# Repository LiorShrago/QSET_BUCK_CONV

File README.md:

# QSET_BUCK_CONV
Buck Converter which can have an input votlage of 12V-9V and then step-down the voltage to 5V. There is also an E-Fuse on the output of the Buck converter for extra safety.

Inside the folder there are 3 more folder.
1 - One folder that all the EAGLE library files needed to see the schematic

2 - One folder holds the EAGLE schematic and PCB files

3 - One folder has the TinaTi, spice files used to test the buck converter before manufcaturing the PCB. TinaTi is a spice software that TI offers for their components,
it helped check that the Buck converter transient response and how bad its Output Voltage ripple would be under various loads.

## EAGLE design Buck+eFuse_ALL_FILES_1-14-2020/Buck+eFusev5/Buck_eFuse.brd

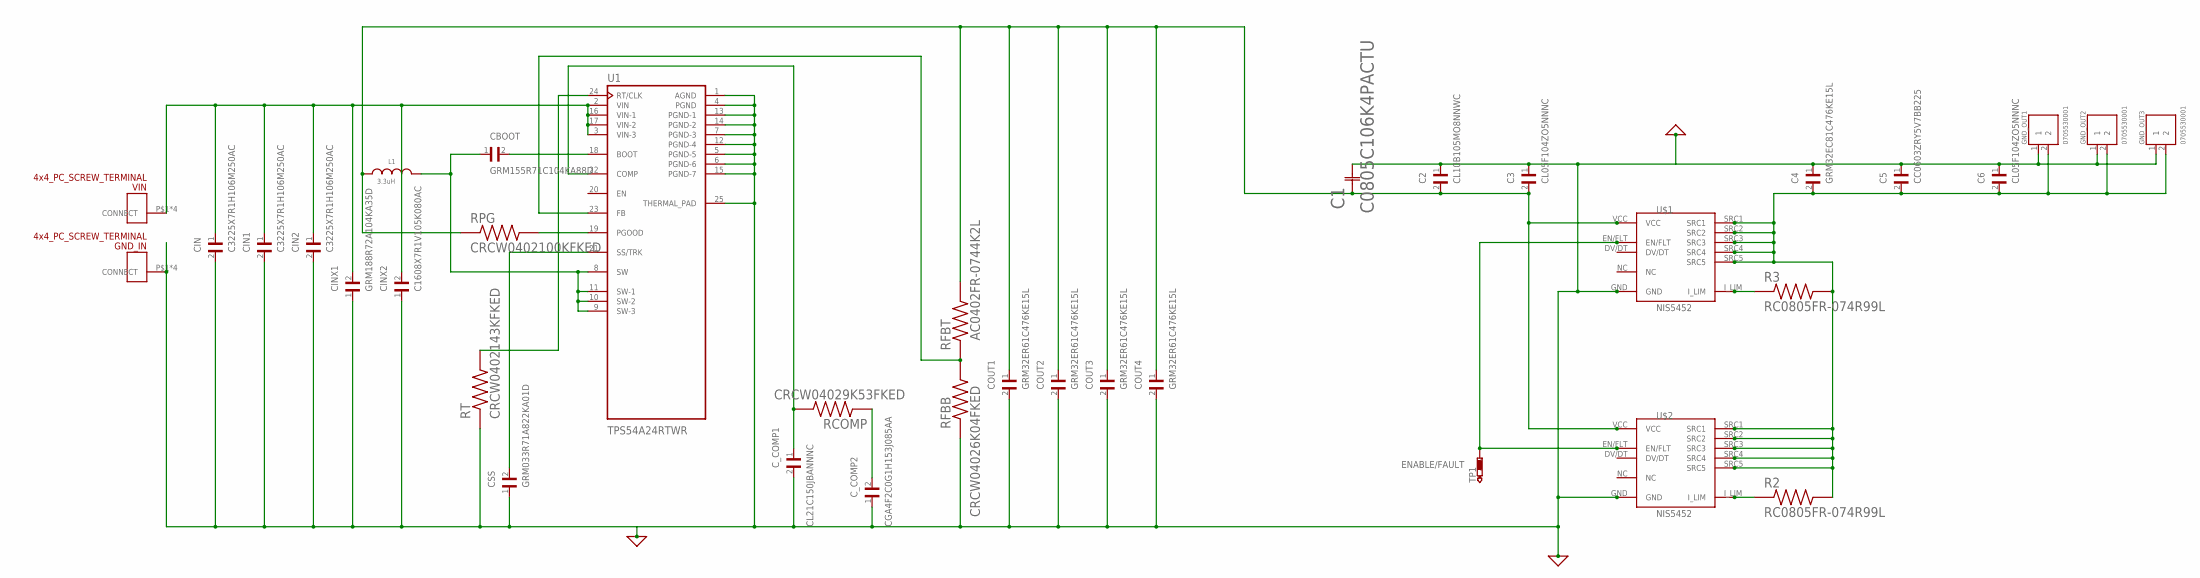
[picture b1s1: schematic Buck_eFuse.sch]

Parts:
C1: C0805C106K4PACTU; CAP_C0805
C2: CL10B105MO8NNWC; CAPC1608X90N
C3, C6: CL05F104ZO5NNNC; CAPC1005X55N
C4: GRM32EC81C476KE15L; CAPC3225X270N
C5: CC0603ZRY5V7BB225; CAPC1608X90
CBOOT: GRM155R71C104KA88D; CAPC1005X55N
CIN, CIN1, CIN2: C3225X7R1H106M250AC; CAPC3225X280N
CINX1: GRM188R72A104KA35D; CAPC1608X90N
CINX2: C1608X7R1V105K080AC; CAPC1608X90N
COUT1, COUT2, COUT3, COUT4: GRM32ER61C476KE15L; CAPC3225X270N
CSS: GRM033R71A822KA01D; CAPC0603X33N
C_COMP1: CL21C150JBANNNC; CAPC2012X140N
C_COMP2: CGA4F2C0G1H153J085AA; CAPC2012X100N
GND_IN: 2X2_PC_SCREW_TERMINAL; SCREW_TERMINAL
GND_OUT1, GND_OUT2, GND_OUT3: 0705530001; MOLEX_0705530001
L1: 3.3uH; WE-HCC_1090
R2, R3: RC0805FR-074R99L; RESC2012X60N
RCOMP: CRCW04029K53FKED; RESC1005X40N
RFBB: CRCW04026K04FKED; RESC1005X40N
RFBT: AC0402FR-0744K2L; RESC1005X37N
RPG: CRCW0402100KFKED; RESC1005X40N
RT: CRCW0402143KFKED; RESC1005X40N
TP1: PTR1B2,54; B2,54
U1: TPS54A24RTWR; VQFN50P400X400X100-24N
U$1, U$2: NIS5452; WDFN10
VIN: 2X2_PC_SCREW_TERMINAL; SCREW_TERMINAL

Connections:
0: C1.2, C2.1, C3.1, C4.1, C5.1, C6.1, CIN.2, CIN1.2, CIN2.2, CINX1.1, CINX2.1, COUT1.2, COUT2.2, COUT3.2, COUT4.2, CSS.1, C_COMP1.2, C_COMP2.1, GND_IN.P$1, GND_IN.P$2, GND_IN.P$3, GND_IN.P$4, GND_OUT1.1, GND_OUT2.1, GND_OUT3.1, RFBB.1, RT.1, U1.1 (AGND), U1.4 (PGND), U1.5 (PGND-5), U1.6 (PGND-6), U1.7 (PGND-3), U1.12 (PGND-4), U1.13 (PGND-1), U1.14 (PGND-2), U1.15 (PGND-7), U1.25 (THERMAL_PAD), U$1.GND, U$2.GND
ENABLE/FAULT: TP1.TP, U$1.EN/FLT, U$2.EN/FLT
unnamed: CBOOT.2, U1.18 (BOOT)
unnamed: CBOOT.1, L1.2, U1.8 (SW), U1.9 (SW-3), U1.10 (SW-2), U1.11 (SW-1)
unnamed: R3.1, U$1.I_LIM
unnamed: R2.1, U$2.I_LIM
unnamed: CSS.2, U1.21 (SS/TRK)
unnamed: RT.2, U1.24 (RT/CLK)
unnamed: RPG.2, U1.19 (PGOOD)
unnamed: RFBB.2, RFBT.1, U1.23 (FB)
unnamed: C_COMP1.1, RCOMP.1, U1.22 (COMP)
unnamed: C_COMP2.2, RCOMP.2
unnamed: CIN.1, CIN1.1, CIN2.1, CINX1.2, CINX2.2, U1.2 (VIN), U1.3 (VIN-3), U1.16 (VIN-1), U1.17 (VIN-2), VIN.P$1, VIN.P$2, VIN.P$3, VIN.P$4
unnamed: C1.1, C2.2, C3.2, COUT1.1, COUT2.1, COUT3.1, COUT4.1, L1.1, RFBT.2, RPG.1, U$1.VCC, U$2.VCC
V_OUT: C4.2, C5.2, C6.2, GND_OUT1.2, GND_OUT2.2, GND_OUT3.2, R2.2, R3.2, U$1.SRC1, U$1.SRC2, U$1.SRC3, U$1.SRC4, U$1.SRC5, U$2.SRC1, U$2.SRC2, U$2.SRC3, U$2.SRC4, U$2.SRC5

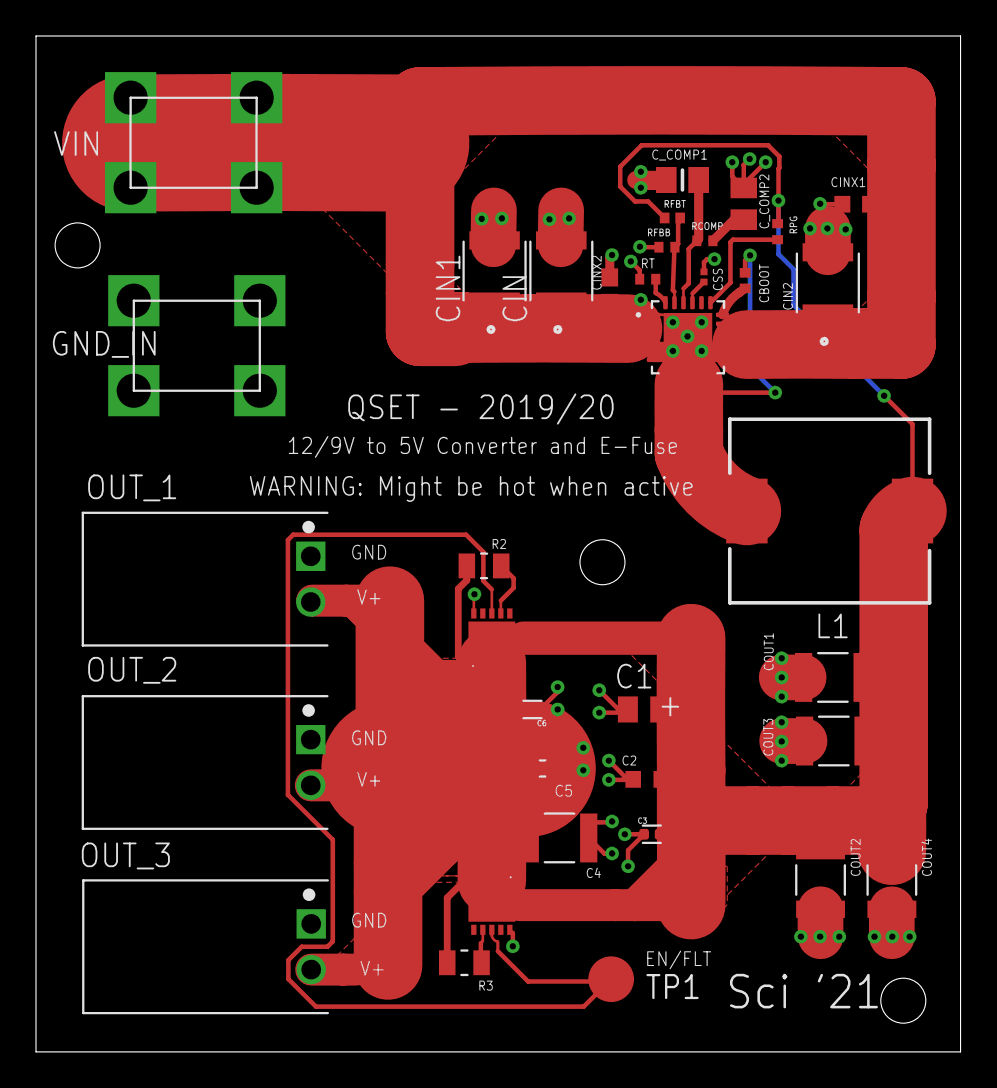
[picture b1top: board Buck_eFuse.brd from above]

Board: 2 copper layers, 51.4 x 56.4 mm, 36 parts (0 on the bottom side), 15 nets.

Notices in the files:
parts and their libraries:
Eagle_WE-HCC: Copyright: Würth Elektronik
